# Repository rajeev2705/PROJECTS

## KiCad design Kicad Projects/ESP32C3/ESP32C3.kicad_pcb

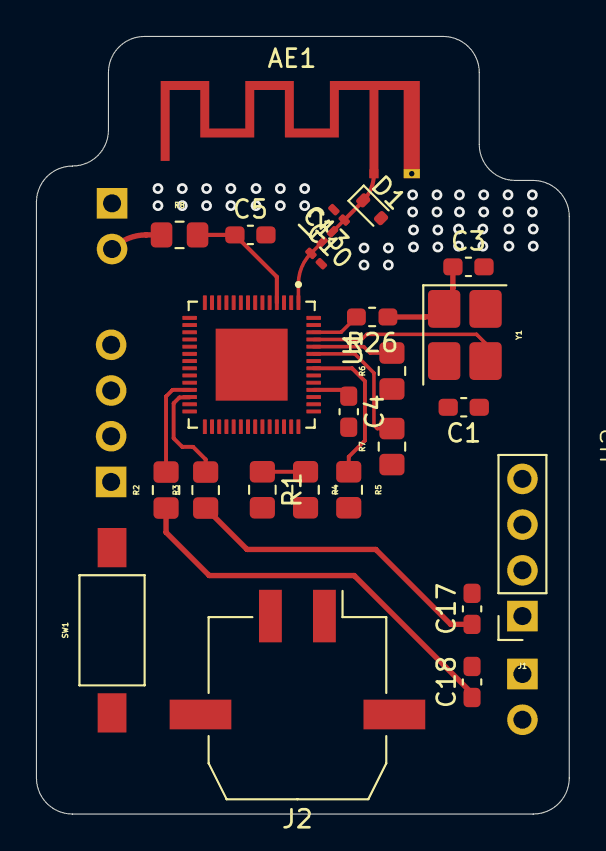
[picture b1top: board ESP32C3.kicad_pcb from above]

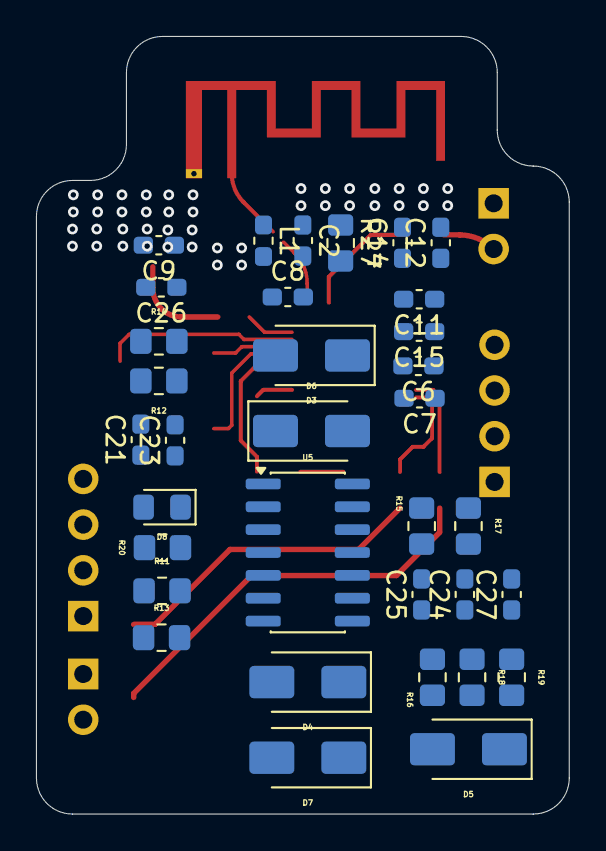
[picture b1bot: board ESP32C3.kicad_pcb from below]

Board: 4 copper layers, 29.6 x 43.2 mm, 60 parts (34 on the bottom side), 35 nets.

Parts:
AE1: Antenna_Chip; Texas_SWRA117D_2.4GHz_Left
C1, C3: 10pf; C_0603_1608Metric_Pad1.08x0.95mm_HandSolder
C2, C6, C15: 10uf; C_0603_1608Metric_Pad1.08x0.95mm_HandSolder
C4, C7, C11, C12, C17, C18: 0.1uf; C_0603_1608Metric_Pad1.08x0.95mm_HandSolder
C5, C8, C14, C26, C27: 1uf; C_0603_1608Metric_Pad1.08x0.95mm_HandSolder
C9, C23, C25: 100nf; C_0603_1608Metric_Pad1.08x0.95mm_HandSolder
C10: 1.2pf; C_0201_0603Metric_Pad0.64x0.40mm_HandSolder
C13: 1.8pf; C_0201_0603Metric_Pad0.64x0.40mm_HandSolder
C21, C24: 4.7uf; C_0603_1608Metric_Pad1.08x0.95mm_HandSolder
D1: ESD5Zxx; D_SOD-523
D3, D4, D5, D6: 1N4148; D_SMA
D7: D_Schottky; D_SMA
D8: LED; LED_0805_2012Metric_Pad1.15x1.40mm_HandSolder
J1: Conn_01x04_Socket; PinSocket_1x04_P2.54mm_Vertical
J2: Conn_01x02_Pin; Molex_Micro-Fit_3.0_43650-0212_1x02-1MP_P3.00mm_Horizontal
L1: 600 Ω @ 100 MHz >500mA; L_0603_1608Metric_Pad1.05x0.95mm_HandSolder
L2: 2.4nH; L_0201_0603Metric_Pad0.64x0.40mm_HandSolder
R1: 15k; R_0805_2012Metric_Pad1.20x1.40mm_HandSolder
R2, R3: 22R; R_0805_2012Metric_Pad1.20x1.40mm_HandSolder
R4, R6, R7, R8, R15, R16, R17, R18, R19, R20, R27: 10k; R_0805_2012Metric_Pad1.20x1.40mm_HandSolder
R5: 499R; R_0805_2012Metric_Pad1.20x1.40mm_HandSolder
R11, R13: 100k; R_0805_2012Metric_Pad1.20x1.40mm_HandSolder
R12: 6.8k; R_0805_2012Metric_Pad1.20x1.40mm_HandSolder
R14: 1k; R_0805_2012Metric_Pad1.20x1.40mm_HandSolder
R26: 0R; L_0603_1608Metric_Pad1.05x0.95mm_HandSolder
SW1: SW_SPST; SW_SPST_FSMSM
U1: ESP32-S3FN8; QFN40P700X700X90-57N
U2: Power_Suply_User
U5: LM324; SOIC-14_3.9x8.7mm_P1.27mm
Y1: upto 40 Mhz =+-10ppm; Crystal_SMD_3225-4Pin_3.2x2.5mm_HandSoldering

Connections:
/-3V3: C24.1, C25.1, U2.A8 (3V3), U5.11 (V-)
/ECHO: J1.3, R4.2
/TDS_IN: J2.1, R12.1, U5.1
/TDS_OUT: J2.2, R11.2, R13.1, U5.6 (-)
Cas-3v3: C2.1, C4.1, C21.1, C23.1, L1.1, R8.1, R20.2, R27.1, U1.2 (VDD3P3), U1.3 (VDD3P3), U1.20 (VDD3P3_RTC), U1.29 (VDD_SPI), U1.46 (VDD3P3_CPU), U1.55 (VDDA1), U1.56 (VDDA2), U2.A7 (-3v3), U5.4 (V+)
Cas-5V: J1.1, U2.A6 (5V)
Cas-gnd: AE1.2 (PCB_Trace), C1.2, C2.2, C3.2, C4.2, C5.2, C6.2, C7.2, C8.2, C9.2, C10.2, C11.2, C12.2, C13.2, C14.2, C15.2, C17.2, C18.2, C21.2, C23.2, C24.2, C25.2, C26.2, C27.2, D1.2 (A), D7.2 (A), D8.1 (K), J1.4, R1.2, R6.1, R7.1, R11.1, SW1.1 (A), U2.A4 (GND), U2.A5 (GND), U5.3 (+), U5.5 (+), U5.10 (+), Y1.2, Y1.4
EN: C5.1, R8.2, U1.4 (CHIP_PU)
GPIO0: R27.2, SW1.2 (B), U1.5 (GPIO0), U2.A3 (SIG)
GPIO4: R1.1, R4.1, U1.9 (GPIO4)
GPIO5: J1.2, U1.10 (GPIO5)
GPIO6: R14.2, U1.11 (GPIO6)
GPIO7: C27.1, D7.1 (K), R19.1, U1.12 (GPIO7)
GPIO19: R2.2, U1.25 (GPIO19)
GPIO20: R3.2, U1.26 (GPIO20)
GPIO45: R7.2, U1.51 (GPIO45)
GPIO46: R6.2, U1.52 (GPIO46)
LNA_IN: C10.1, L2.1, U1.1 (LNA_IN)
unnamed: AE1.1 (FEED), C13.1, D1.1 (K), L2.2
unnamed: C3.1, R26.1, Y1.1
unnamed: C6.1, C7.1, C8.1, C11.1, C12.1, C14.1, C15.1, L1.2
unnamed: D3.2 (A), R17.1, U5.13 (-)
unnamed: D3.1 (K), D6.2 (A), U5.14
unnamed: D4.2 (A), R16.2, R18.1, U5.9 (-)
unnamed: D4.1 (K), D5.2 (A), U5.8
unnamed: C26.1, D5.1 (K), D6.1 (K), R17.2, R18.2, R19.2
unnamed: D8.2 (A), R20.1
unnamed: R13.2, R15.1, R16.1, U5.7
unnamed: R5.1, U1.49 (U0TXD)
unnamed: C9.1, R12.2, R14.1, U5.2 (-)
unnamed: R15.2, U5.12 (+)
XTAL_N: C1.1, U1.53 (XTAL_N), Y1.3
XTAL_P: R26.2, U1.54 (XTAL_P)
cas+: C17.1, R3.1, U2.A2 (D+)
cas-: C18.1, R2.1, U2.A1 (D-)

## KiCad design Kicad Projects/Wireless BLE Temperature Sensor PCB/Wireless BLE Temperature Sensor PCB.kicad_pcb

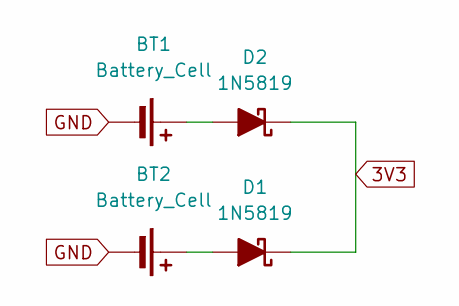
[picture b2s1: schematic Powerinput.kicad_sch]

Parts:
BT1, BT2: Battery_Cell; BatteryHolder_MYOUNG_BS-07-A1BJ001_CR2032; LCSC No. C5239862
D1, D2: 1N5819; D_DO-41_SOD81_P10.16mm_Horizontal; LCSC No. C402218

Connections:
3V3: D1.1 (K), D2.1 (K); also elsewhere on the board
GND: BT1.2 (-), BT2.2 (-); also elsewhere on the board
unnamed: BT1.1 (+), D2.2 (A)
unnamed: BT2.1 (+), D1.2 (A)

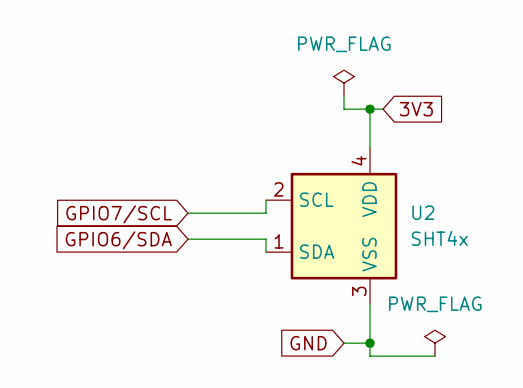
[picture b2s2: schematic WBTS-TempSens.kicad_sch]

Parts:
U2: SHT4x; PinHeader_1x04_P2.54mm_Vertical; LCSC No. C32713270

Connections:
3V3: U2.4 (VDD); also elsewhere on the board
GND: U2.3 (VSS); also elsewhere on the board
GPIO6/SDA: U2.1 (SDA); also elsewhere on the board
GPIO7/SCL: U2.2 (SCL); also elsewhere on the board

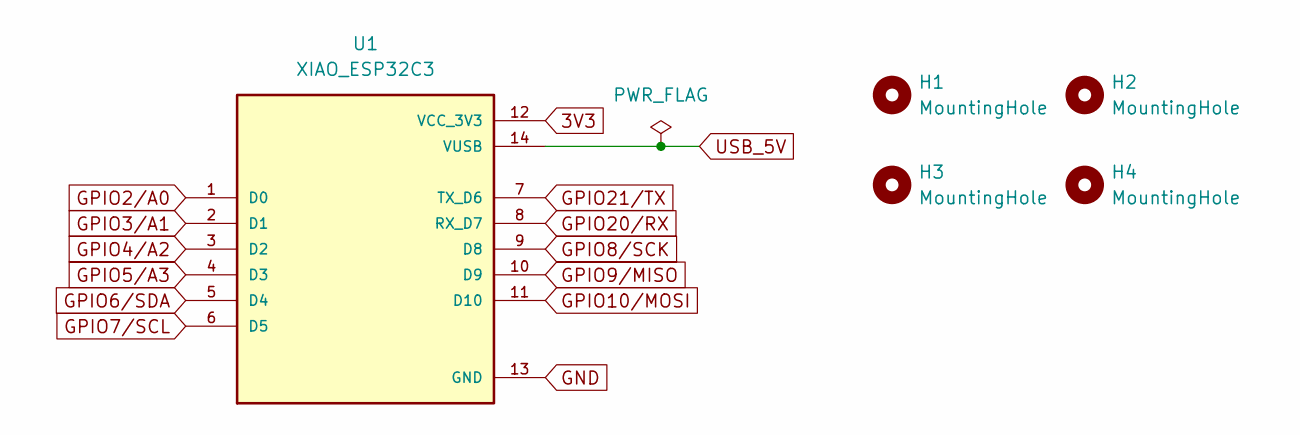
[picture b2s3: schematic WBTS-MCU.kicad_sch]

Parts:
H1, H2, H3, H4: MountingHole; MountingHole_2.2mm_M2
U1: XIAO_ESP32C3; MODULE_XIAO_ESP32C3; PARTREV 23/05/2022; LCSC No. C32713273

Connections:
3V3: U1.12 (VCC_3V3); also elsewhere on the board
GND: U1.13 (GND); also elsewhere on the board
GPIO2/A0: U1.1 (D0)
GPIO3/A1: U1.2 (D1)
GPIO4/A2: U1.3 (D2)
GPIO5/A3: U1.4 (D3)
GPIO6/SDA: U1.5 (D4); also elsewhere on the board
GPIO7/SCL: U1.6 (D5); also elsewhere on the board
GPIO8/SCK: U1.9 (D8)
GPIO9/MISO: U1.10 (D9)
GPIO10/MOSI: U1.11 (D10)
GPIO20/RX: U1.8 (RX_D7)
GPIO21/TX: U1.7 (TX_D6)
USB_5V: U1.14 (VUSB)

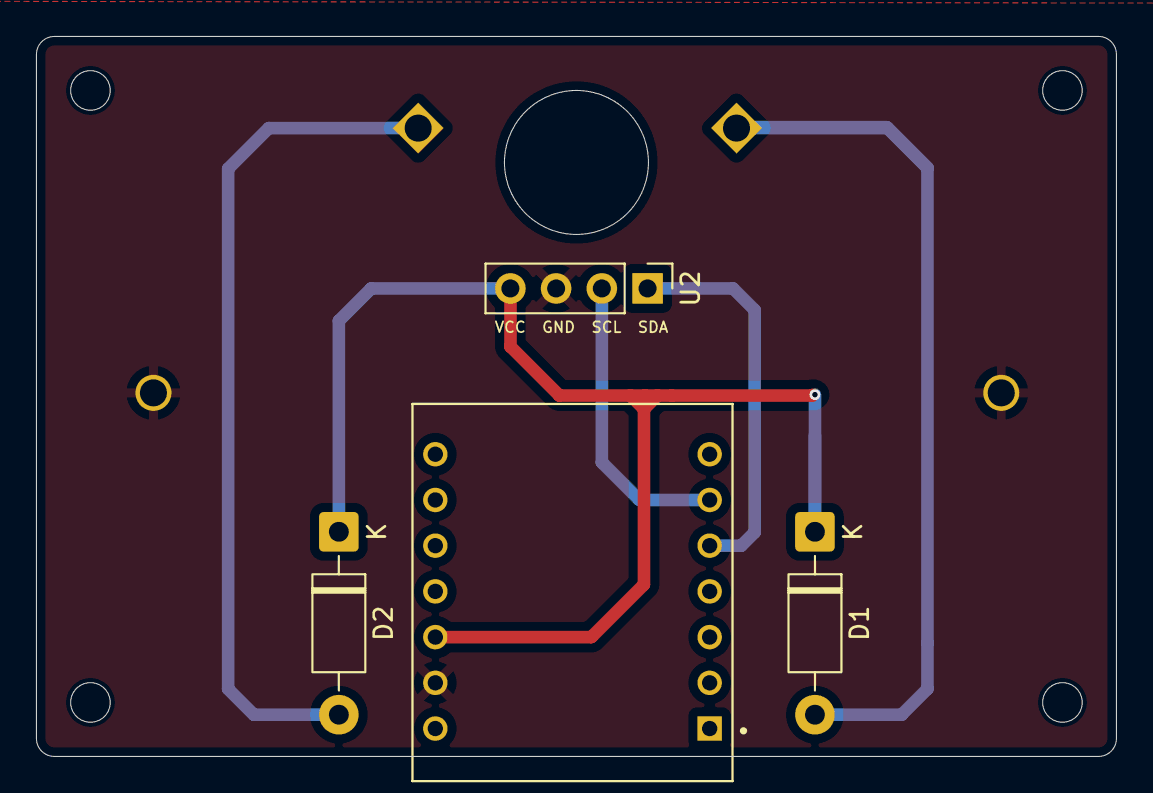
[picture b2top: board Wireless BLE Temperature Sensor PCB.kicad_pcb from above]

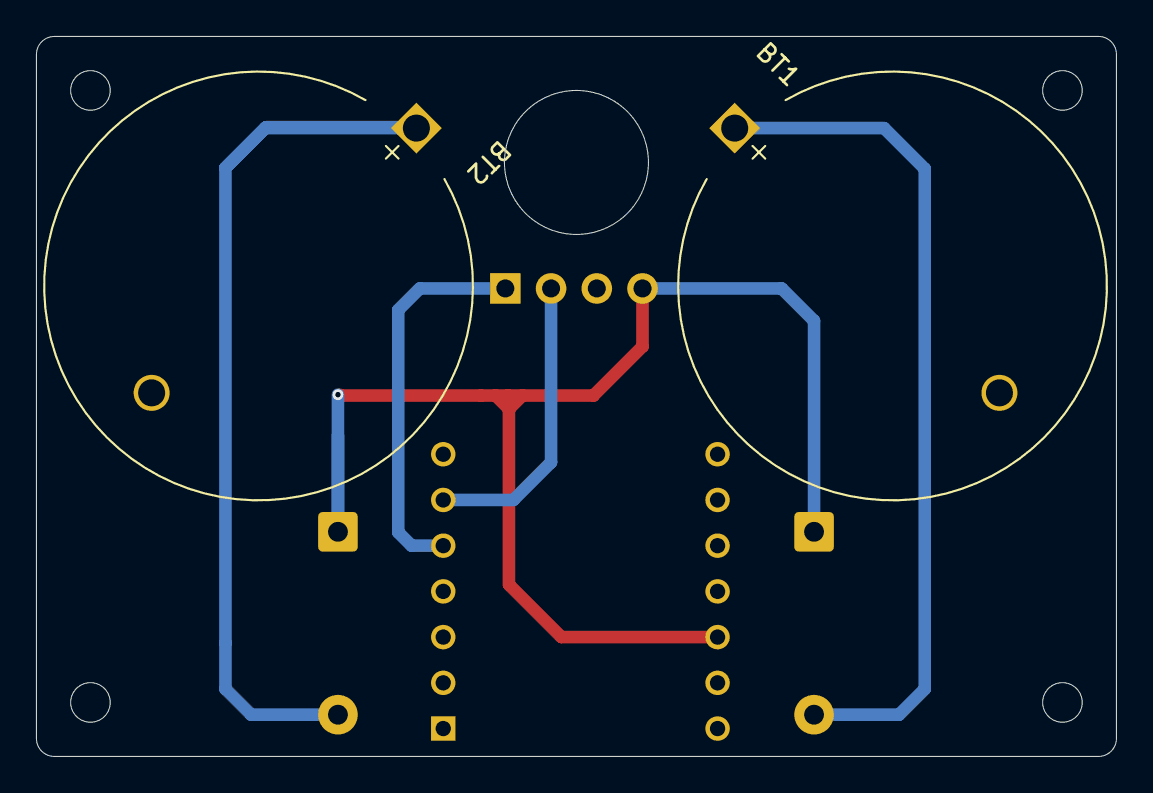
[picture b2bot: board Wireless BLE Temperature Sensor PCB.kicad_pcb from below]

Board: 2 copper layers, 60.0 x 40.0 mm, 10 parts (2 on the bottom side), 6 nets.

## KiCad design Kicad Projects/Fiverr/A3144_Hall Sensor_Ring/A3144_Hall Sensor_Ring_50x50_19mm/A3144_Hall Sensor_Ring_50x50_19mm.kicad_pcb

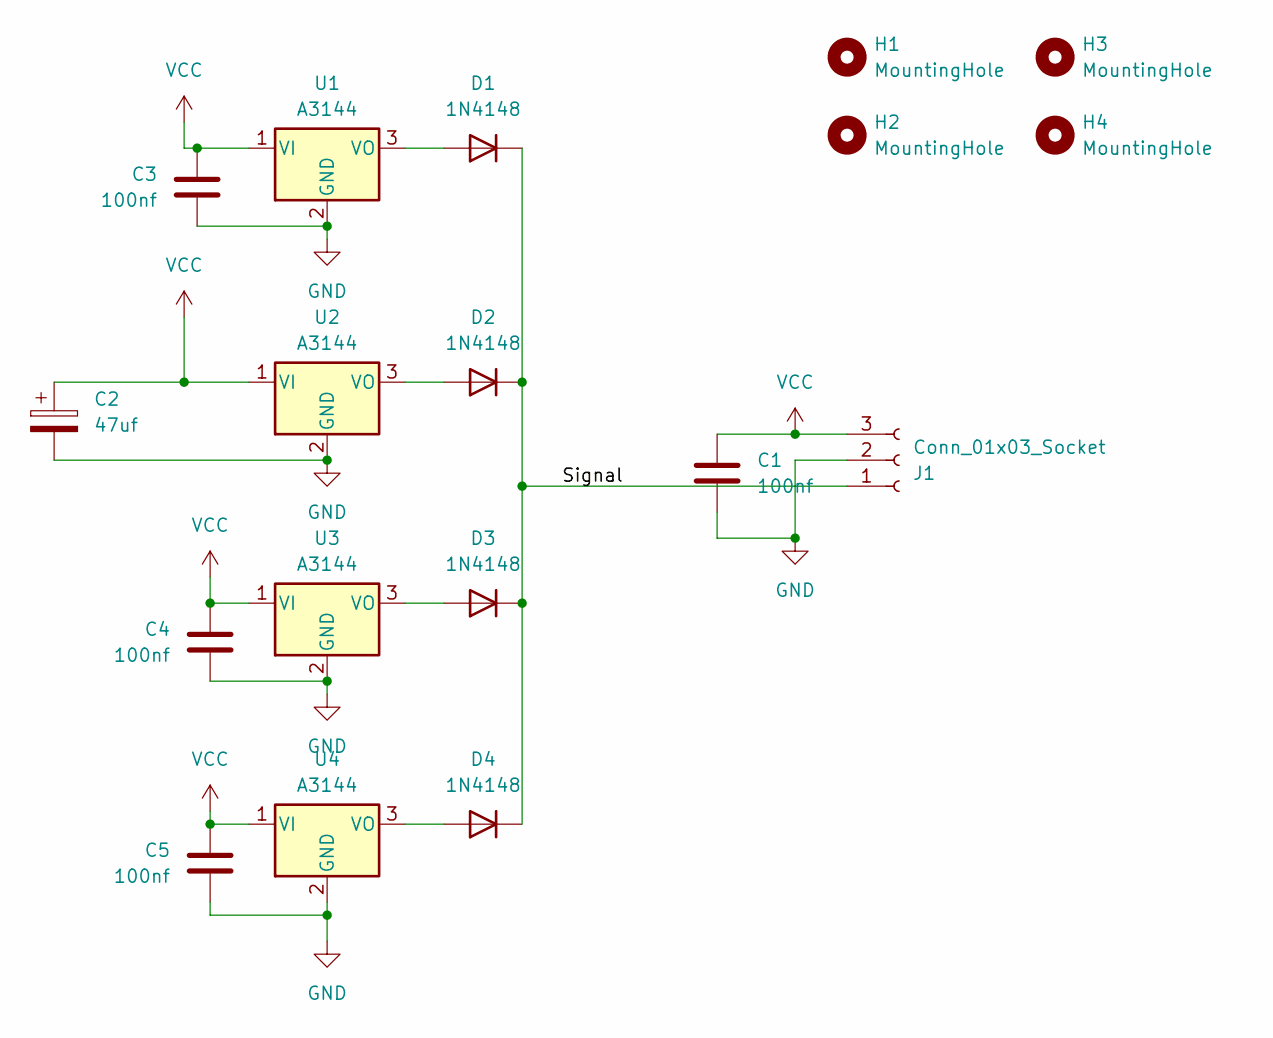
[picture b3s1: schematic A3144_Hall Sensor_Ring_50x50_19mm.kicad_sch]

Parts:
C1, C3, C4, C5: 100nf; C_Disc_D3.0mm_W1.6mm_P2.50mm
C2: 47uf; CP_Radial_D5.0mm_P2.50mm
D1, D2, D3, D4: 1N4148; D_DO-35_SOD27_P7.62mm_Horizontal
H1, H2, H3, H4: MountingHole; MountingHole_5.5mm
J1: Conn_01x03_Socket; JST_EH_S3B-EH_1x03_P2.50mm_Horizontal
U1, U2, U3, U4: A3144; TO-92_Inline new

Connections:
/Signal: D1.1 (K), D2.1 (K), D3.1 (K), D4.1 (K), J1.1
GND: C1.2, C2.2, C3.2, C4.2, C5.2, J1.2, U1.2 (GND), U2.2 (GND), U3.2 (GND), U4.2 (GND)
unnamed: D1.2 (A), U1.3 (VO)
unnamed: D2.2 (A), U2.3 (VO)
unnamed: D3.2 (A), U3.3 (VO)
unnamed: D4.2 (A), U4.3 (VO)
VCC: C1.1, C2.1, C3.1, C4.1, C5.1, J1.3, U1.1 (VI), U2.1 (VI), U3.1 (VI), U4.1 (VI)

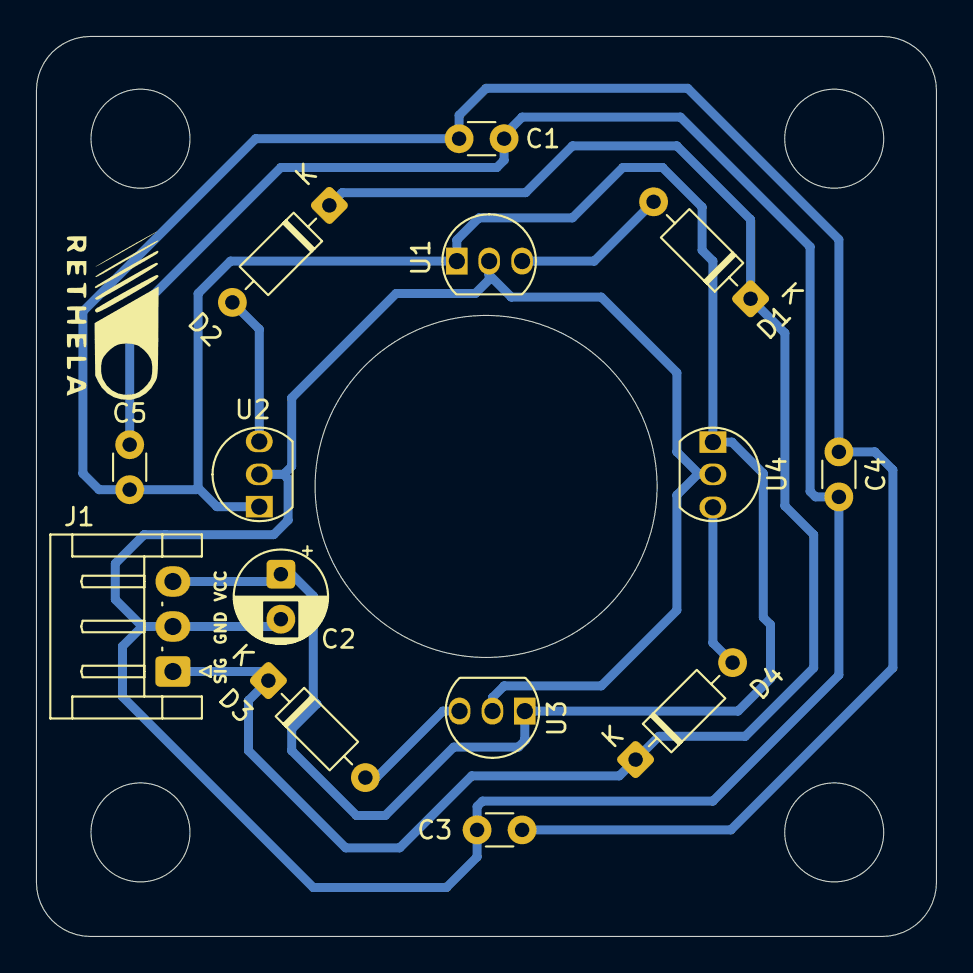
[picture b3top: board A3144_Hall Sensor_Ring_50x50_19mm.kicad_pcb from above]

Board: 2 copper layers, 50.0 x 50.0 mm, 18 parts (0 on the bottom side), 7 nets.

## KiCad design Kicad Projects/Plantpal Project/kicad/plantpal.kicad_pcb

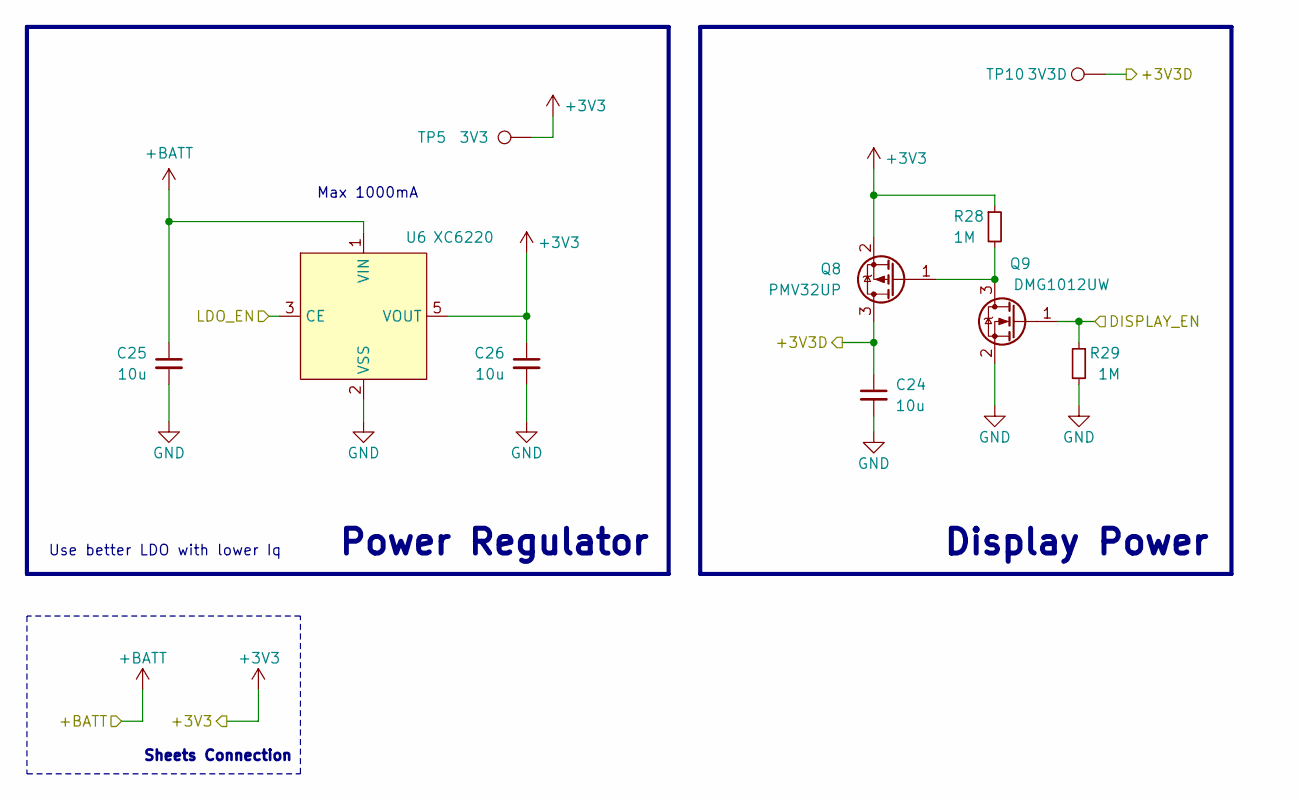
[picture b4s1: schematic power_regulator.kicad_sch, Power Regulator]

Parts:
C24, C25, C26: 10u; C_0603_1608Metric; Part Description Ceramic Capacitor 10V 10uF X5R ±10% 0603
Q8: PMV32UP; SOT-23; Part Description MOSFET P Channel 20V 4A 52mΩ@4.5V
Q9: DMG1012UW; SOT-323_SC-70; Part Description MOSFET N Channel 20V 1A 450mΩ@4.5V 600m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
R28, R29: 1M; R_0402_1005Metric; Part Description Resistor 62.5mW ±1% 1MΩ
TP5: 3V3; TestPoint_Pad_D1.0mm
TP10: 3V3D; TestPoint_Pad_D1.0mm
U6: XC6220; SOT-23-5; Part Description LDO Voltage Regulators 1A

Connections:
+3V3: C26.1, Q8.2 (S), R28.1, TP5.1, U6.5 (VOUT); also elsewhere on the board
+BATT: C25.1, U6.1 (VIN); also elsewhere on the board
/+3V3D: C24.1, Q8.3 (D), TP10.1; also elsewhere on the board
/Main Controller/DISPLAY_EN: Q9.1 (G), R29.1; also elsewhere on the board
/Power Regulator/LDO_EN: U6.3 (CE); also elsewhere on the board
GND: C24.2, C25.2, C26.2, Q9.2 (S), R29.2, U6.2 (VSS); also elsewhere on the board
unnamed: Q8.1 (G), Q9.3 (D), R28.2

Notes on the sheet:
Use better LDO with lower Iq
Max 1000mA
Display Power
Sheets Connection
Power Regulator

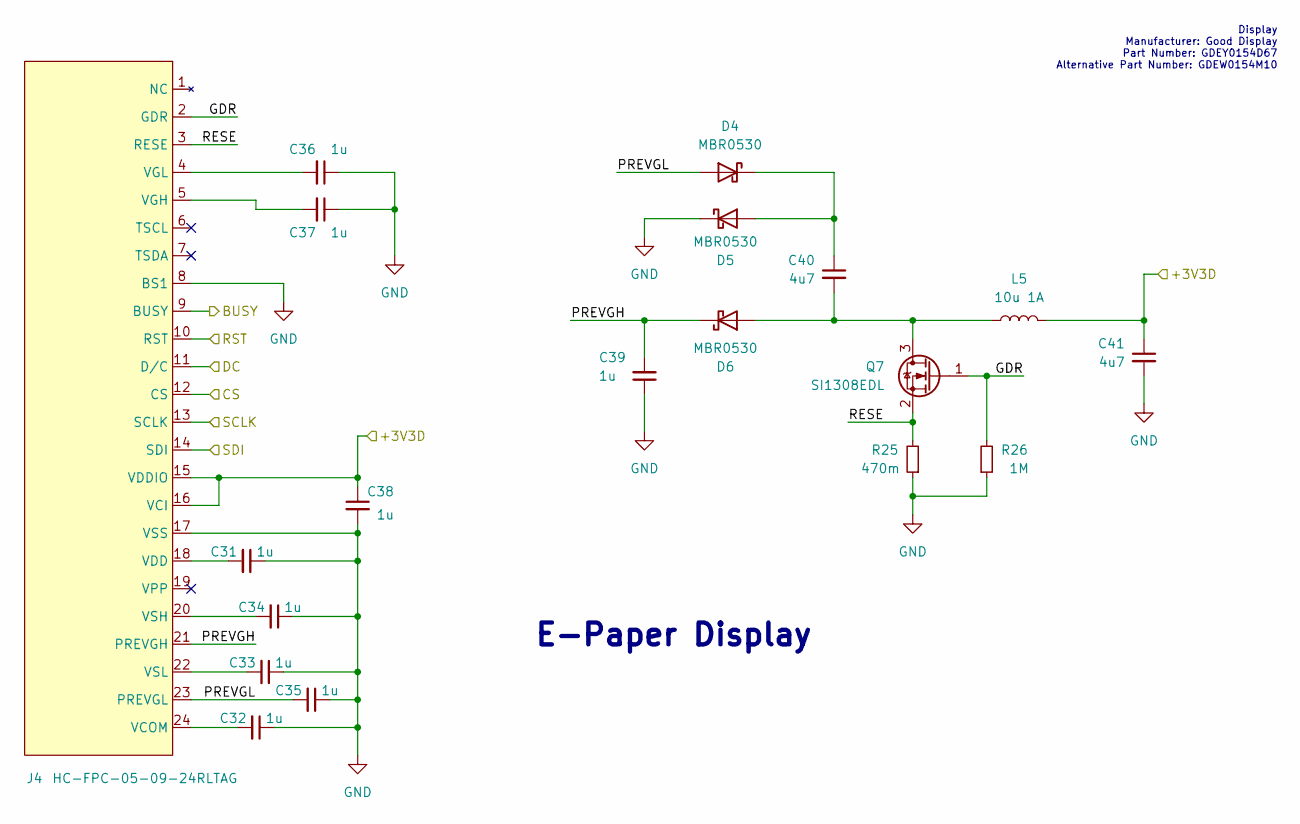
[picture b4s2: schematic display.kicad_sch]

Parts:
C31, C32, C33, C34, C35, C36, C37, C38, C39: 1u; C_0402_1005Metric; Part Description Ceramic Capacitors 50V 1uF X5R ±10%
C40, C41: 4u7; C_0603_1608Metric; Part Description Ceramic Capacitors 25V 4.7uF X5R ±10%
D4, D5, D6: MBR0530; D_SOD-123; Part Description Schottky Barrier Diodes 30V 430mV@500mA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
J4: HC-FPC-05-09-24RLTAG; FPC-SMD_24P-P0.50_HC-FPC-05-09-24RLTAG; Part Description FFC & FPC Connectors Clamshell 24P Bott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
L5: 10u 1A; L_Changjiang_FNR4012S; Part Description Power Inductors 1A 10uH ±20% 1.1A SMD,4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
Q7: SI1308EDL; SOT-323_SC-70; Part Description MOSFET N Channel 30V 1.4A 132mΩ@10V,1.4A
R25: 470m; R_0402_1005Metric; Part Description Resistor 125mW ±1% 470mΩ
R26: 1M; R_0402_1005Metric; Part Description Resistors 100mW ±1% 1MΩ

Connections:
/+3V3D: C38.1, C41.1, J4.15 (VDDIO), J4.16 (VCI), L5.1; also elsewhere on the board
/Display/BUSY: J4.9 (BUSY); also elsewhere on the board
/Display/CS: J4.12 (CS); also elsewhere on the board
/Display/DC: J4.11 (D/C); also elsewhere on the board
/Display/GDR: J4.2 (GDR), Q7.1 (G), R26.2
/Display/PREVGH: C39.2, D6.1 (K), J4.21 (PREVGH)
/Display/PREVGL: C35.2, D4.2 (A), J4.23 (PREVGL)
/Display/RESE: J4.3 (RESE), Q7.2 (S), R25.2
/Display/RST: J4.10 (RST); also elsewhere on the board
/Display/SCLK: J4.13 (SCLK); also elsewhere on the board
/Display/SDI: J4.14 (SDI); also elsewhere on the board
GND: C31.1, C32.1, C33.1, C34.1, C35.1, C36.1, C37.1, C38.2, C39.1, C41.2, D5.1 (K), J4.8 (BS1), J4.17 (VSS), R25.1, R26.1; also elsewhere on the board
unnamed: C40.1, D4.1 (K), D5.2 (A)
unnamed: C40.2, D6.2 (A), L5.2, Q7.3 (D)
unnamed: C32.2, J4.24 (VCOM)
unnamed: C31.2, J4.18 (VDD)
unnamed: C37.2, J4.5 (VGH)
unnamed: C36.2, J4.4 (VGL)
unnamed: C34.2, J4.20 (VSH)
unnamed: C33.2, J4.22 (VSL)

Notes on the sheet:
Display Manufacturer: Good Display Part Number: GDEY0154D67 Alternative Part Number: GDEW0154M10
E-Paper Display

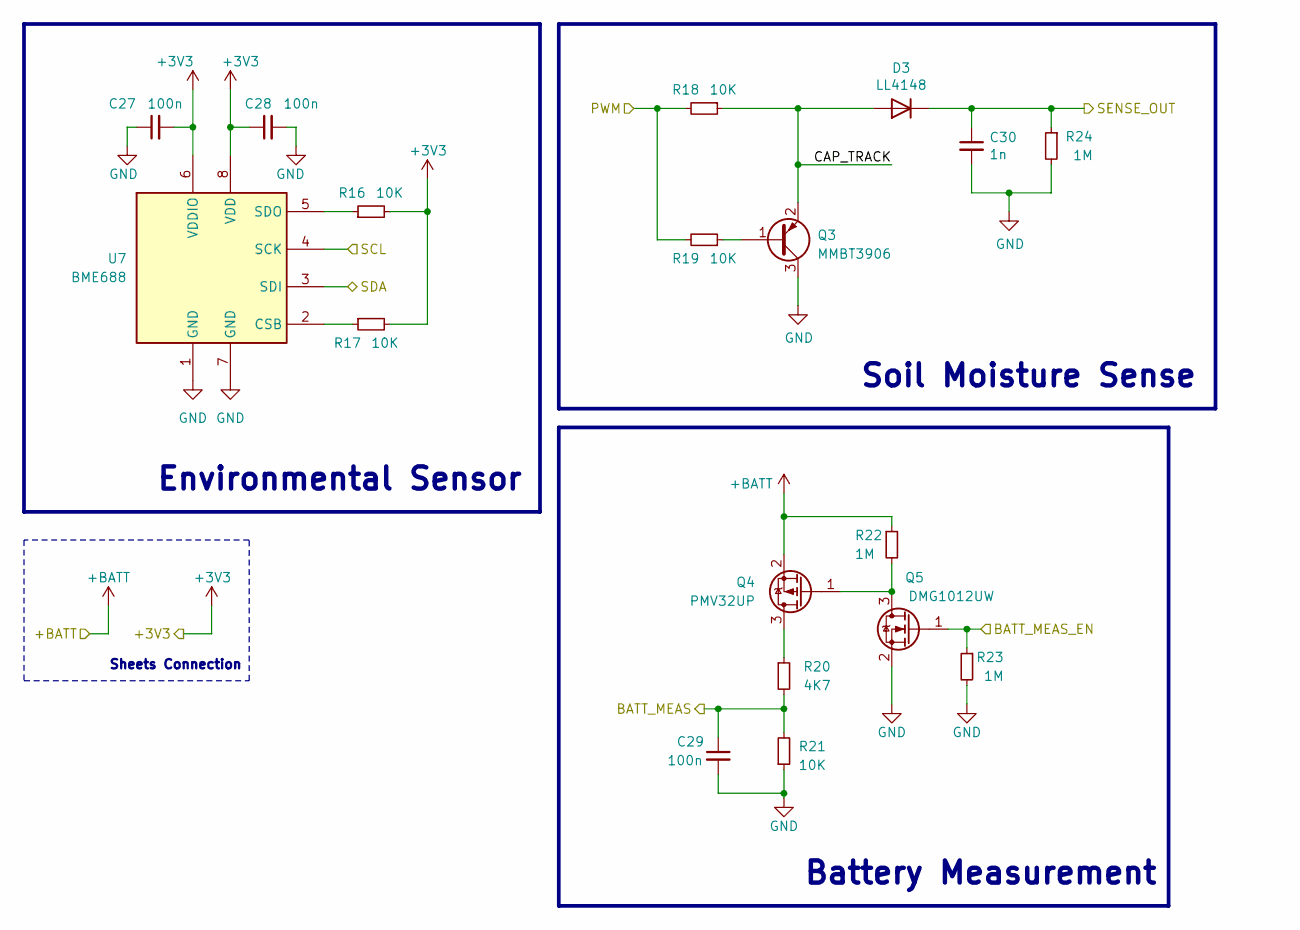
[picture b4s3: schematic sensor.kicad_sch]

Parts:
C27, C28, C29: 100n; C_0402_1005Metric; Part Description Ceramic Capacitor 16V 100nF X7R ±10%
C30: 1n; C_0402_1005Metric; Part Description Ceramic Capacitors 50V 1nF X7R ±10%
D3: LL4148; D_MiniMELF; Part Description Switching Diode 75V 500mW 1V@10mA 4ns 0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
Q3: MMBT3906; SOT-23; Part Description Bipolar Transistors 40V 200mW 100@10mA,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
Q4: PMV32UP; SOT-23; Part Description MOSFET P Channel 20V 4A 52mΩ@4.5V
Q5: DMG1012UW; SOT-323_SC-70; Part Description MOSFET N Channel 20V 1A 450mΩ@4.5V 600m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
R16, R17, R18, R19, R21: 10K; R_0402_1005Metric; Part Description Resistors 62.5mW ±1% 10kΩ
R20: 4K7; R_0402_1005Metric; Part Description Resistor 62.5mW ±1% 4.7kΩ
R22, R23, R24: 1M; R_0402_1005Metric; Part Description Resistor 62.5mW ±1% 1MΩ
U7: BME688; BME680-PSON80P300X300X100-8N; Part Description Gas, Humidity, Pressure, Temperature Se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

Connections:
+3V3: C27.2, C28.1, R16.2, R17.2, U7.6 (VDDIO), U7.8 (VDD); also elsewhere on the board
+BATT: Q4.2 (S), R22.1; also elsewhere on the board
/Main Controller/BATT_MEAS: C29.1, R20.2, R21.2; also elsewhere on the board
/Main Controller/BATT_MEAS_EN: Q5.1 (G), R23.1; also elsewhere on the board
/Main Controller/PWM: R18.2, R19.2; also elsewhere on the board
/Main Controller/SENSE_OUT: C30.1, D3.1 (K), R24.1; also elsewhere on the board
/SCL: U7.4 (SCK); also elsewhere on the board
/SDA: U7.3 (SDI); also elsewhere on the board
/Sensor/CAP_TRACK: D3.2 (A), Q3.2 (E), R18.1
GND: C27.1, C28.2, C29.2, C30.2, Q3.3 (C), Q5.2 (S), R21.1, R23.2, R24.2, U7.1 (GND), U7.7 (GND); also elsewhere on the board
unnamed: Q3.1 (B), R19.1
unnamed: Q4.3 (D), R20.1
unnamed: Q4.1 (G), Q5.3 (D), R22.2
unnamed: R17.1, U7.2 (CSB)
unnamed: R16.1, U7.5 (SDO)

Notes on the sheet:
Sheets Connection
Soil Moisture Sense
Battery Measurement
Environmental Sensor

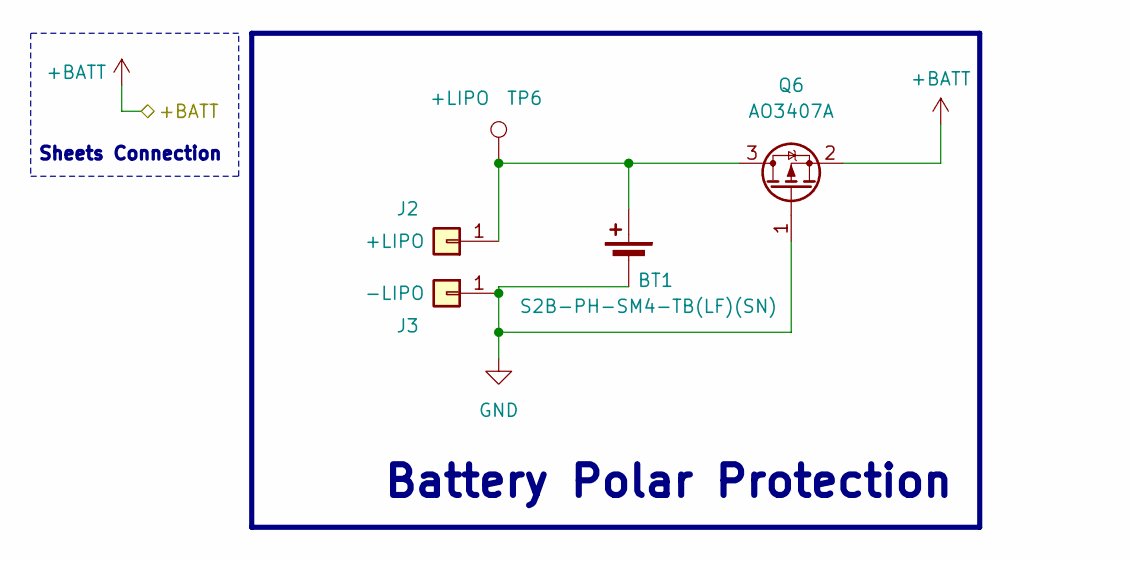
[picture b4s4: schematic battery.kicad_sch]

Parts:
BT1: S2B-PH-SM4-TB(LF)(SN); JST_PH_S2B-PH-SM4-TB_1x02-1MP_P2.00mm_Horizontal; Part Description Wire To Board Connector 1x2P PH 2mm Mal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
J2: +LIPO; TestPoint_THTPad_D1.0mm_Drill0.5mm; Part Description On-board Pad
J3: -LIPO; TestPoint_THTPad_D1.0mm_Drill0.5mm; Part Description On-board Pad
Q6: AO3407A; SOT-23; Part Description MOSFET P Channel 30V 4.3A 48mΩ@10V,4.3A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
TP6: +LIPO; TestPoint_Pad_D1.0mm

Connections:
+BATT: Q6.2 (S); also elsewhere on the board
GND: BT1.2 (-), J3.1, Q6.1 (G); also elsewhere on the board
unnamed: BT1.1 (+), J2.1, Q6.3 (D), TP6.1

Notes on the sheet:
Battery Polar Protection
Sheets Connection

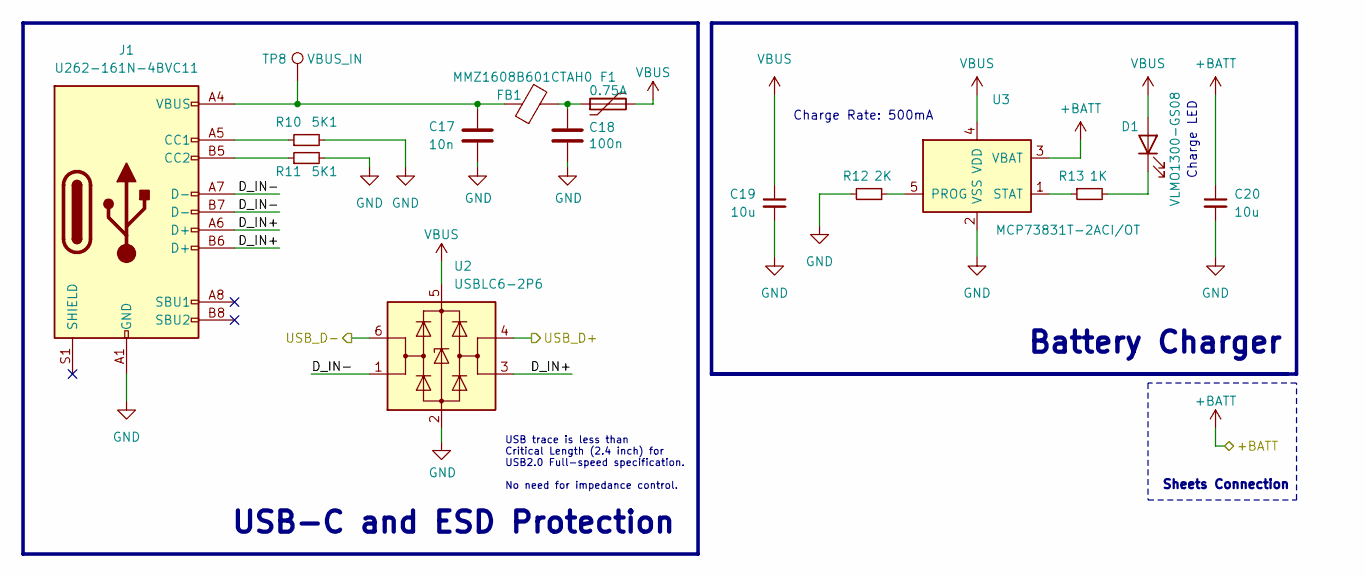
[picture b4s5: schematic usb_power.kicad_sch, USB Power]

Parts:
C17: 10n; C_0402_1005Metric; Part Description Ceramic Capacitors 16V 10nF X7R ±10%
C18: 100n; C_0402_1005Metric; Part Description Ceramic Capacitor 16V 100nF X7R ±10%
C19, C20: 10u; C_0603_1608Metric; Part Description Ceramic Capacitor 10V 10uF X5R ±10% 0603
D1: VLMO1300-GS08; LED_0603_1608Metric; Part Description Orange 2V 20mA
F1: 0.75A; Fuse_0805_2012Metric; Part Description Resettable Fuses 6V 750mA 40A 1.5A
FB1: MMZ1608B601CTAH0; L_0603_1608Metric; Part Description Ferrite Beads 400mΩ ±25% 600Ω@100MHz
J1: U262-161N-4BVC11; USB_C_Receptacle_XKB_U262-16XN-4BVC11; Part Description USB Connectors Type-C 3A USB 3.1 16P
R10, R11: 5K1; R_0402_1005Metric; Part Description Resistor 62.5mW ±1% 5.1kΩ
R12: 2K; R_0402_1005Metric; Part Description Resistor 62.5mW ±1% 2kΩ
R13: 1K; R_0402_1005Metric; Part Description Resistor 62.5mW ±1% 1kΩ
TP8: VBUS_IN; TestPoint_Pad_D1.0mm
U2: USBLC6-2P6; SOT50P160X60-6N; Part Description ESD Protection 6V 17V 2 Unidirectional 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
U3: MCP73831T-2ACI/OT; SOT-23-5; Part Description Battery Management IC 6V LiPoly 1500mA

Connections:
+BATT: C20.1, U3.3 (VBAT); also elsewhere on the board
/Main Controller/USB_D+: U2.4 (I/O2); also elsewhere on the board
/Main Controller/USB_D-: U2.6 (I/O1); also elsewhere on the board
/USB Power/D_IN+: J1.A6 (D+), J1.B6 (D+), U2.3 (I/O2)
/USB Power/D_IN-: J1.A7 (D-), J1.B7 (D-), U2.1 (I/O1)
GND: C17.2, C18.2, C19.2, C20.2, J1.A1 (GND), J1.A12 (GND), J1.B1 (GND), J1.B12 (GND), R10.2, R11.2, R12.2, U2.2 (GND), U3.2 (VSS); also elsewhere on the board
unnamed: C17.1, FB1.1, J1.A4 (VBUS), J1.A9 (VBUS), J1.B4 (VBUS), J1.B9 (VBUS), TP8.1
unnamed: C18.1, F1.1, FB1.2
unnamed: D1.1 (K), R13.2
unnamed: J1.A5 (CC1), R10.1
unnamed: J1.B5 (CC2), R11.1
unnamed: R12.1, U3.5 (PROG)
unnamed: R13.1, U3.1 (STAT)
VBUS: C19.1, D1.2 (A), F1.2, U2.5 (VBUS), U3.4 (VDD)

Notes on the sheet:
Sheets Connection
Charge Rate: 500mA
Battery Charger
USB-C and ESD Protection
Charge LED
USB trace is less than Critical Length (2.4 inch) for USB2.0 Full-speed specification. No need for impedance control.

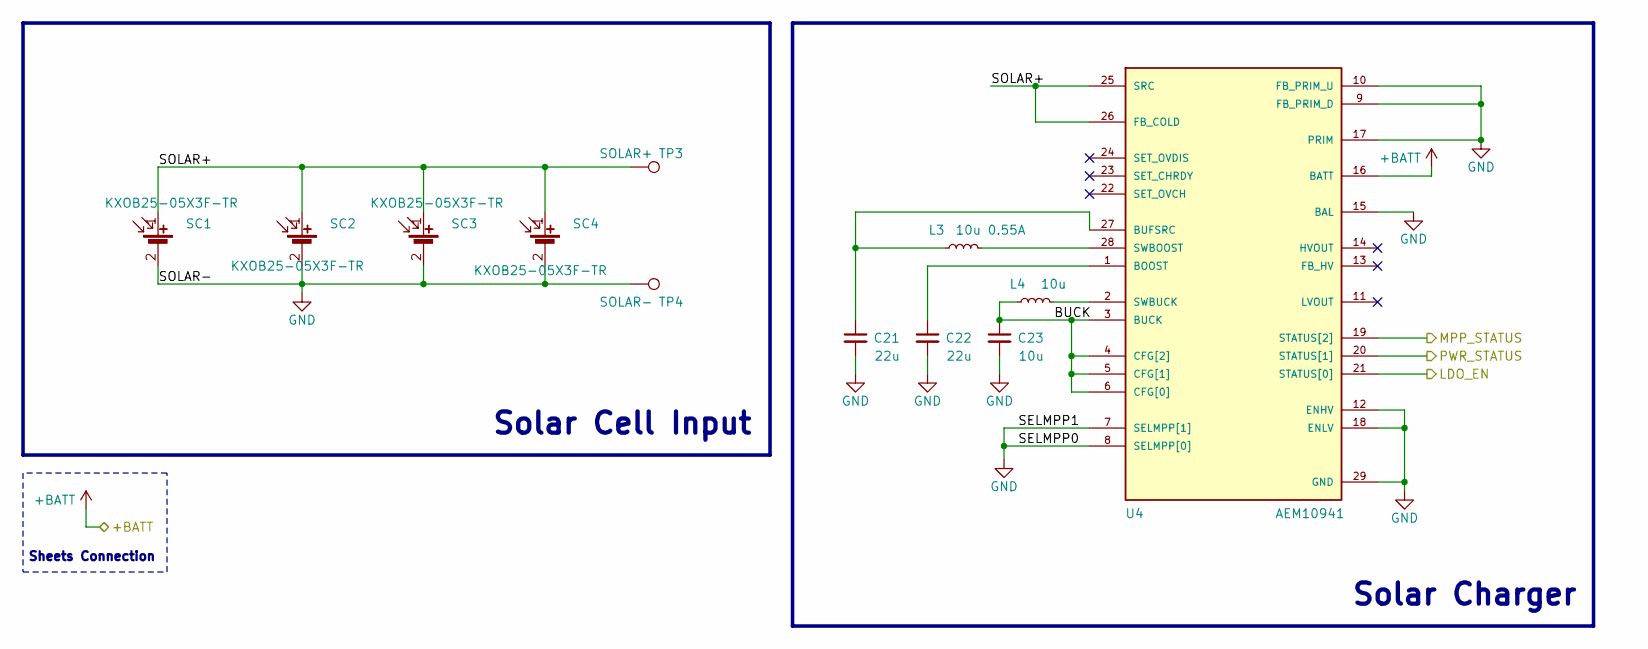
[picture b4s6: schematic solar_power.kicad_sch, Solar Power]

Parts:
C21, C22: 22u; C_0603_1608Metric; Part Description Ceramic Capacitors 10V 22uF X5R ±20%
C23: 10u; C_0603_1608Metric; Part Description Ceramic Capacitor 10V 10uF X5R ±10%
L3: 10u 0.55A; IND_LPS4012-103MRB; Part Description Power Inductors - SMD 10uH Shld 20% 1.1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
L4: 10u; L_0603_1608Metric; Part Description Power Inductors 10uH ±20% 90mA 1.05Ω
SC1, SC2, SC3, SC4: KXOB25-05X3F-TR; KXOB25-05X3F; Part Description Solar Cell G3 Thin 2.07V 30.7MW
TP3: SOLAR+; TestPoint_Pad_D1.0mm
TP4: SOLAR-; TestPoint_Pad_D1.0mm
U4: AEM10941; QFN-28-1EP_5x5mm_P0.5mm_EP3.35x3.35mm; Part Description PMIC IC - Photovoltaic Energy Harvestin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

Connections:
+BATT: U4.16 (BATT); also elsewhere on the board
/Main Controller/MPP_STATUS: U4.19 (STATUS[2]); also elsewhere on the board
/Main Controller/PWR_STATUS: U4.20 (STATUS[1]); also elsewhere on the board
/Power Regulator/LDO_EN: U4.21 (STATUS[0]); also elsewhere on the board
/Solar Power/BUCK: C23.1, L4.1, U4.3 (BUCK), U4.4 (CFG[2]), U4.5 (CFG[1]), U4.6 (CFG[0])
/Solar Power/SOLAR+: SC1.1 (+), SC2.1 (+), SC3.1 (+), SC4.1 (+), TP3.1, U4.25 (SRC), U4.26 (FB_COLD)
GND: C21.2, C22.2, C23.2, SC1.2 (-), SC2.2 (-), SC3.2 (-), SC4.2 (-), TP4.1, U4.7 (SELMPP[1]), U4.8 (SELMPP[0]), U4.9 (FB_PRIM_D), U4.10 (FB_PRIM_U), U4.12 (ENHV), U4.15 (BAL), U4.17 (PRIM), U4.18 (ENLV), U4.29 (GND); also elsewhere on the board
unnamed: C22.1, U4.1 (BOOST)
unnamed: C21.1, L3.1, U4.27 (BUFSRC)
unnamed: L3.2, U4.28 (SWBOOST)
unnamed: L4.2, U4.2 (SWBUCK)

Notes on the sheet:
Solar Cell Input
Sheets Connection
Solar Charger
